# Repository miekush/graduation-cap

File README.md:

# Graduation Cap
A simple LED sequencer based Graduation Cap

This is a pretty simple LED Graduation cap reference design I made for the upcoming graduation ceremony of my BSEE! It's circuit is based on my [N-Output Sequencer](https://github.com/mkengineering/N_Output_Sequencer) reference design and could be easily modified for other students to use in their own ceremony.

# Gerber View

# Tassel Holder

Unfortunatly I wasn't able to get good measurements of the original button that holds the tassel on top of the cap prior to designing the PCB, so the hole I added for it to pass through ended up being too small :cry:. To remedy this, I designed a glue-in 3D printable loop to tie the tassel around. Definitely not ideal but it works great for what it is! Check out the Tassel Holder folder for the solidworks design file and stl!

Designed by Mike Kushnerik (MKE) in KiCad V5

# License

MKE supports the open source hardware community by sharing hardware design files freely on GitHub!

Please support MKE by purchasing products on [Tindie](https://www.tindie.com/stores/mkengineering/)!

Designed by Mike Kushnerik for MKEngineering

Licensed under [Creative Commons Attribution-ShareAlike CC BY-SA 3.0](http://creativecommons.org/licenses/by-sa/3.0/)

All text above must be included in any redistribution!

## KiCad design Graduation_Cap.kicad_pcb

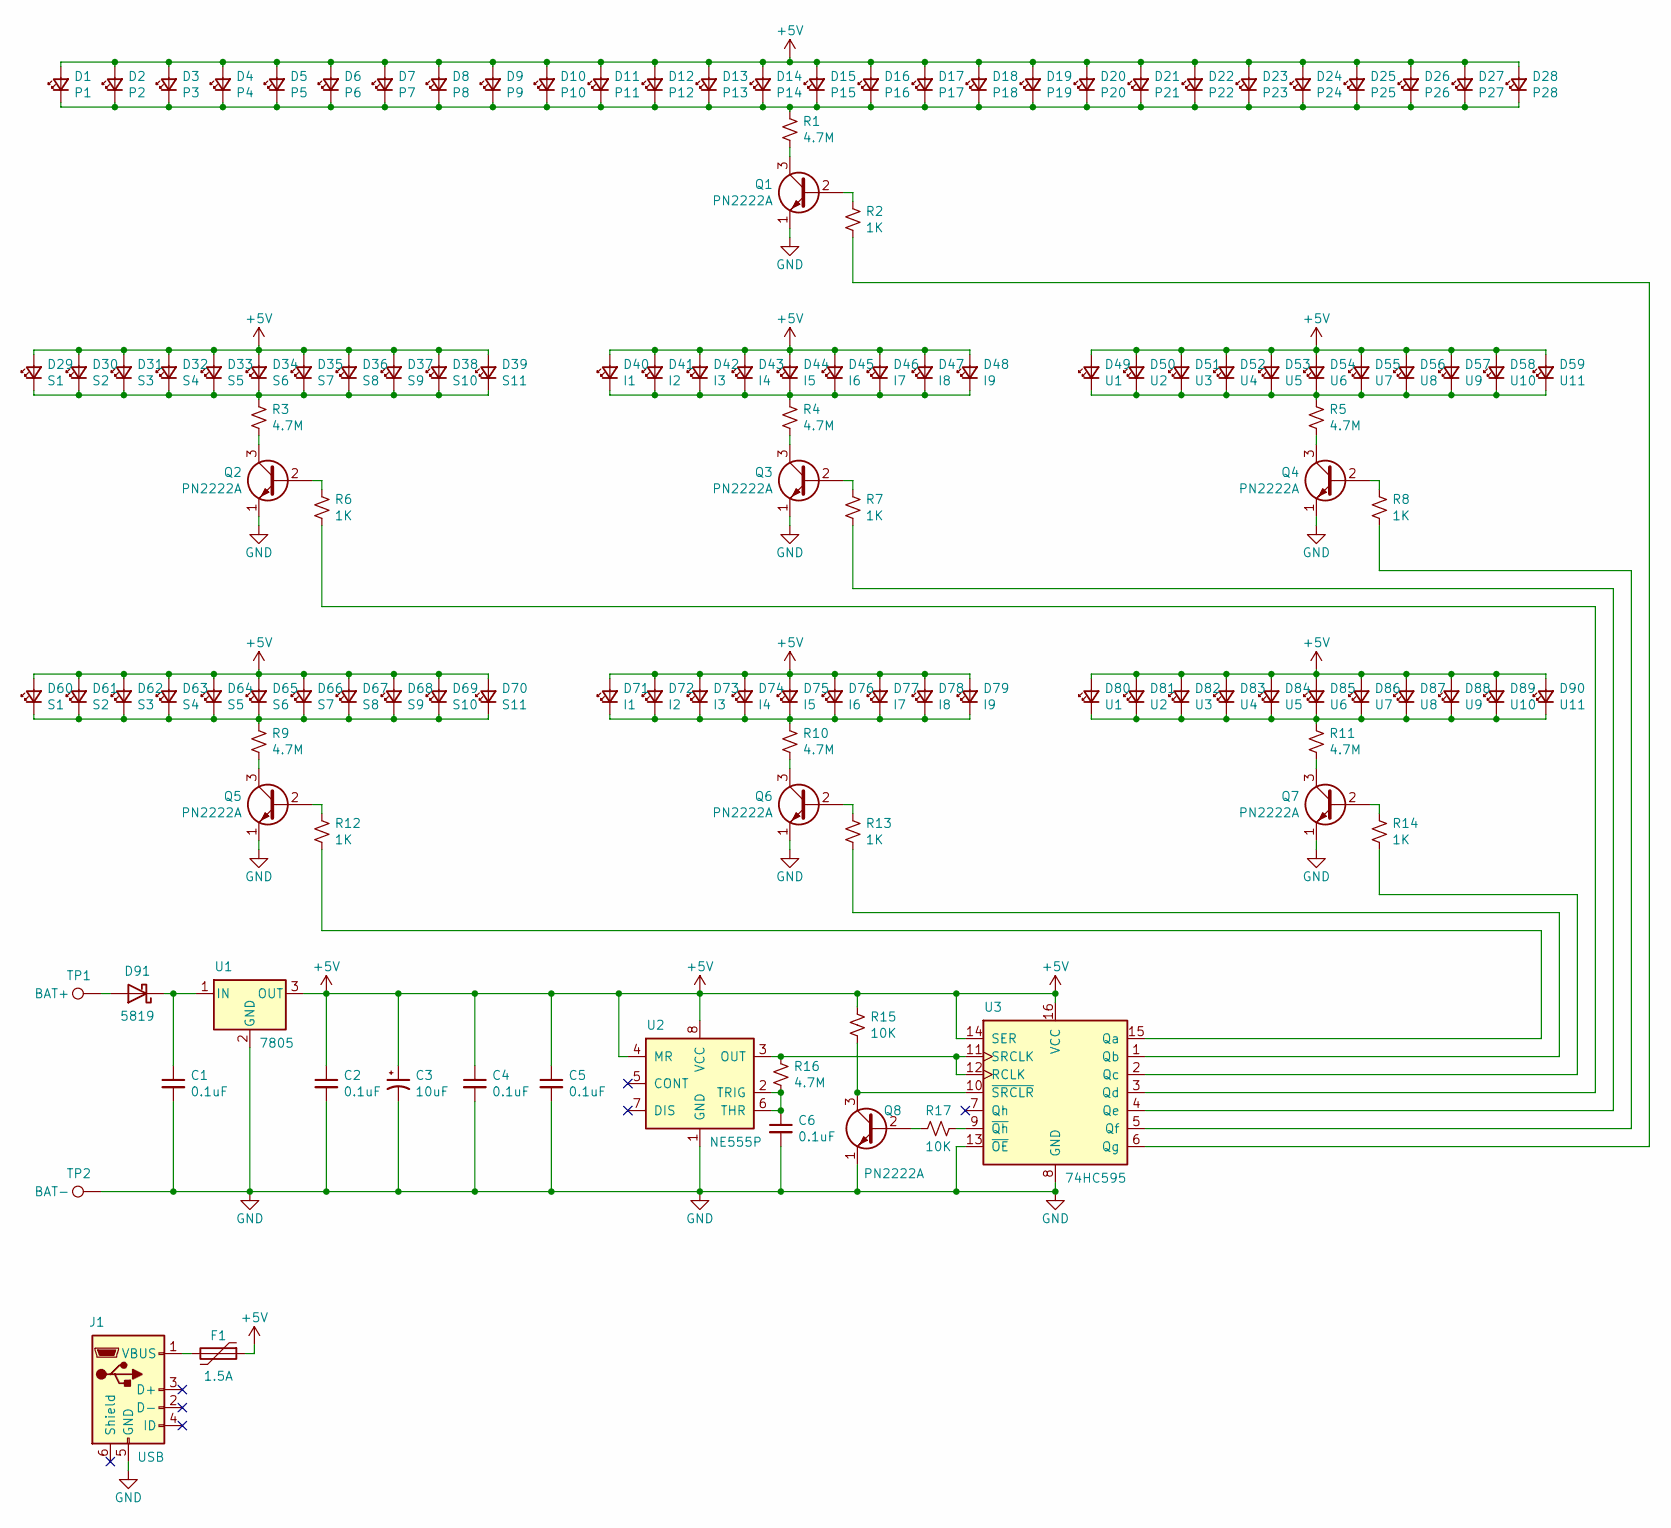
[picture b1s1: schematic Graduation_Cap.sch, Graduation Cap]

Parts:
C1, C2, C4, C5, C6: 0.1uF; C_Disc_D4.3mm_W1.9mm_P5.00mm
C3: 10uF; CP_Radial_D6.3mm_P2.50mm
D1: P1; LED_D3.0mm
D2: P2; LED_D3.0mm
D3: P3; LED_D3.0mm
D4: P4; LED_D3.0mm
D5: P5; LED_D3.0mm
D6: P6; LED_D3.0mm
D7: P7; LED_D3.0mm
D8: P8; LED_D3.0mm
D9: P9; LED_D3.0mm
D10: P10; LED_D3.0mm
D11: P11; LED_D3.0mm
D12: P12; LED_D3.0mm
D13: P13; LED_D3.0mm
D14: P14; LED_D3.0mm
D15: P15; LED_D3.0mm
D16: P16; LED_D3.0mm
D17: P17; LED_D3.0mm
D18: P18; LED_D3.0mm
D19: P19; LED_D3.0mm
D20: P20; LED_D3.0mm
D21: P21; LED_D3.0mm
D22: P22; LED_D3.0mm
D23: P23; LED_D3.0mm
D24: P24; LED_D3.0mm
D25: P25; LED_D3.0mm
D26: P26; LED_D3.0mm
D27: P27; LED_D3.0mm
D28: P28; LED_D3.0mm
D29, D60: S1; LED_D3.0mm
D30, D61: S2; LED_D3.0mm
D31, D62: S3; LED_D3.0mm
D32, D63: S4; LED_D3.0mm
D33, D64: S5; LED_D3.0mm
D34, D65: S6; LED_D3.0mm
D35, D66: S7; LED_D3.0mm
D36, D67: S8; LED_D3.0mm
D37, D68: S9; LED_D3.0mm
D38, D69: S10; LED_D3.0mm
D39, D70: S11; LED_D3.0mm
D40, D71: I1; LED_D3.0mm
D41, D72: I2; LED_D3.0mm
D42, D73: I3; LED_D3.0mm
D43, D74: I4; LED_D3.0mm
D44, D75: I5; LED_D3.0mm
D45, D76: I6; LED_D3.0mm
D46, D77: I7; LED_D3.0mm
D47, D78: I8; LED_D3.0mm
D48, D79: I9; LED_D3.0mm
D49, D80: U1; LED_D3.0mm
D50, D81: U2; LED_D3.0mm
D51, D82: U3; LED_D3.0mm
D52, D83: U4; LED_D3.0mm
D53, D84: U5; LED_D3.0mm
D54, D85: U6; LED_D3.0mm
D55, D86: U7; LED_D3.0mm
D56, D87: U8; LED_D3.0mm
D57, D88: U9; LED_D3.0mm
D58, D89: U10; LED_D3.0mm
D59, D90: U11; LED_D3.0mm
D91: 5819; D_DO-41_SOD81_P7.62mm_Horizontal
F1: 1.5A; C_Disc_D10.0mm_W2.5mm_P5.00mm
J1: USB; USB_Mini-B_Wuerth_65100516121_Horizontal
Q1, Q2, Q3, Q4, Q5, Q6, Q7, Q8: PN2222A; TO-92_Inline_Wide
R1, R3, R4, R5, R9, R10, R11: 4.7M; R_Axial_DIN0207_L6.3mm_D2.5mm_P7.62mm_Horizontal
R2, R6, R7, R8, R12, R13, R14: 1K; R_Axial_DIN0204_L3.6mm_D1.6mm_P5.08mm_Horizontal
R15, R17: 10K; R_Axial_DIN0204_L3.6mm_D1.6mm_P5.08mm_Horizontal
R16: 4.7M; R_Axial_DIN0204_L3.6mm_D1.6mm_P5.08mm_Horizontal
TP1: BAT+; WIRE_SR_C
TP2: BAT-; WIRE_SR_R
U1: 7805; TO-220-3_Horizontal_TabDown
U2: NE555P; DIP-8_W7.62mm
U3: 74HC595; DIP-16_W7.62mm

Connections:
+5V: C2.1, C3.1, C4.1, C5.1, D1.2 (A), D2.2 (A), D3.2 (A), D4.2 (A), D5.2 (A), D6.2 (A), D7.2 (A), D8.2 (A), D9.2 (A), D10.2 (A), D11.2 (A), D12.2 (A), D13.2 (A), D14.2 (A), D15.2 (A), D16.2 (A), D17.2 (A), D18.2 (A), D19.2 (A), D20.2 (A), D21.2 (A), D22.2 (A), D23.2 (A), D24.2 (A), D25.2 (A), D26.2 (A), D27.2 (A), D28.2 (A), D29.2 (A), D30.2 (A), D31.2 (A), D32.2 (A), D33.2 (A), D34.2 (A), D35.2 (A), D36.2 (A), D37.2 (A), D38.2 (A), D39.2 (A), D40.2 (A), D41.2 (A), D42.2 (A), D43.2 (A), D44.2 (A), D45.2 (A), D46.2 (A), D47.2 (A), D48.2 (A), D49.2 (A), D50.2 (A), D51.2 (A), D52.2 (A), D53.2 (A), D54.2 (A), D55.2 (A), D56.2 (A), D57.2 (A), D58.2 (A), D59.2 (A), D60.2 (A), D61.2 (A), D62.2 (A), D63.2 (A), D64.2 (A), D65.2 (A), D66.2 (A), D67.2 (A), D68.2 (A), D69.2 (A), D70.2 (A), D71.2 (A), D72.2 (A), D73.2 (A), D74.2 (A), D75.2 (A), D76.2 (A), D77.2 (A), D78.2 (A), D79.2 (A), D80.2 (A), D81.2 (A), D82.2 (A), D83.2 (A), D84.2 (A), D85.2 (A), D86.2 (A), D87.2 (A), D88.2 (A), D89.2 (A), D90.2 (A), F1.1, R15.1, U1.3 (OUT), U2.4 (MR), U2.8 (VCC), U3.14 (SER), U3.16 (VCC)
GND: C1.2, C2.2, C3.2, C4.2, C5.2, C6.2, J1.5 (GND), Q1.1 (E), Q2.1 (E), Q3.1 (E), Q4.1 (E), Q5.1 (E), Q6.1 (E), Q7.1 (E), Q8.1 (E), TP2.1, U1.2 (GND), U2.1 (GND), U3.8 (GND), U3.13 (~OE)
unnamed: C1.1, D91.1 (K), U1.1 (IN)
unnamed: C6.1, R16.2, U2.2 (TRIG), U2.6 (THR)
unnamed: D1.1 (K), D2.1 (K), D3.1 (K), D4.1 (K), D5.1 (K), D6.1 (K), D7.1 (K), D8.1 (K), D9.1 (K), D10.1 (K), D11.1 (K), D12.1 (K), D13.1 (K), D14.1 (K), D15.1 (K), D16.1 (K), D17.1 (K), D18.1 (K), D19.1 (K), D20.1 (K), D21.1 (K), D22.1 (K), D23.1 (K), D24.1 (K), D25.1 (K), D26.1 (K), D27.1 (K), D28.1 (K), R1.1
unnamed: D29.1 (K), D30.1 (K), D31.1 (K), D32.1 (K), D33.1 (K), D34.1 (K), D35.1 (K), D36.1 (K), D37.1 (K), D38.1 (K), D39.1 (K), R3.1
unnamed: D40.1 (K), D41.1 (K), D42.1 (K), D43.1 (K), D44.1 (K), D45.1 (K), D46.1 (K), D47.1 (K), D48.1 (K), R4.1
unnamed: D49.1 (K), D50.1 (K), D51.1 (K), D52.1 (K), D53.1 (K), D54.1 (K), D55.1 (K), D56.1 (K), D57.1 (K), D58.1 (K), D59.1 (K), R5.1
unnamed: D60.1 (K), D61.1 (K), D62.1 (K), D63.1 (K), D64.1 (K), D65.1 (K), D66.1 (K), D67.1 (K), D68.1 (K), D69.1 (K), D70.1 (K), R9.1
unnamed: D71.1 (K), D72.1 (K), D73.1 (K), D74.1 (K), D75.1 (K), D76.1 (K), D77.1 (K), D78.1 (K), D79.1 (K), R10.1
unnamed: D80.1 (K), D81.1 (K), D82.1 (K), D83.1 (K), D84.1 (K), D85.1 (K), D86.1 (K), D87.1 (K), D88.1 (K), D89.1 (K), D90.1 (K), R11.1
unnamed: D91.2 (A), TP1.1
unnamed: F1.2, J1.1 (VBUS)
unnamed: Q1.2 (B), R2.1
unnamed: Q1.3 (C), R1.2
unnamed: Q2.2 (B), R6.1
unnamed: Q2.3 (C), R3.2
unnamed: Q3.2 (B), R7.1
unnamed: Q3.3 (C), R4.2
unnamed: Q4.2 (B), R8.1
unnamed: Q4.3 (C), R5.2
unnamed: Q5.2 (B), R12.1
unnamed: Q5.3 (C), R9.2
unnamed: Q6.2 (B), R13.1
unnamed: Q6.3 (C), R10.2
unnamed: Q7.2 (B), R14.1
unnamed: Q7.3 (C), R11.2
unnamed: Q8.2 (B), R17.2
unnamed: Q8.3 (C), R15.2, U3.10 (~SRCLR)
unnamed: R2.2, U3.6 (Qg)
unnamed: R6.2, U3.3 (Qd)
unnamed: R7.2, U3.4 (Qe)
unnamed: R8.2, U3.5 (Qf)
unnamed: R12.2, U3.15 (Qa)
unnamed: R13.2, U3.1 (Qb)
unnamed: R14.2, U3.2 (Qc)
unnamed: R16.1, U2.3 (OUT), U3.11 (SRCLK), U3.12 (RCLK)
unnamed: R17.1, U3.9 (~Qh)

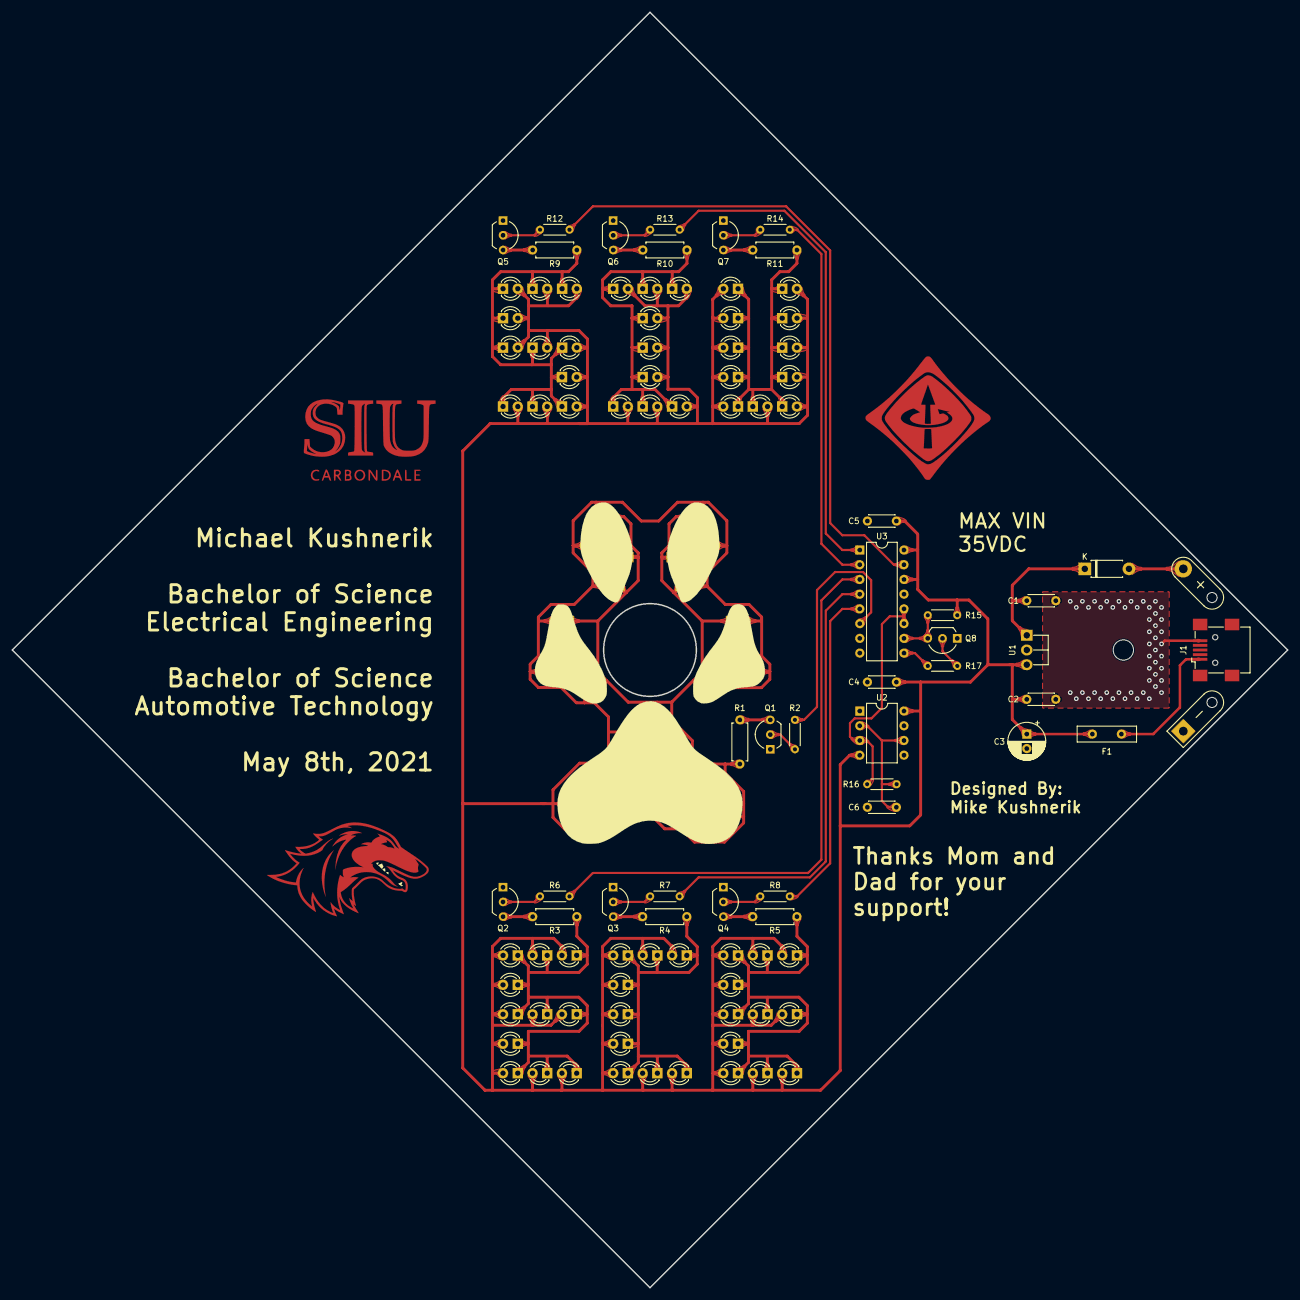
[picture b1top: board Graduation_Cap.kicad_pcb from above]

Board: 2 copper layers, 220.0 x 220.0 mm, 129 parts (0 on the bottom side), 38 nets.

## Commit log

2021-05-05 Initial Upload
